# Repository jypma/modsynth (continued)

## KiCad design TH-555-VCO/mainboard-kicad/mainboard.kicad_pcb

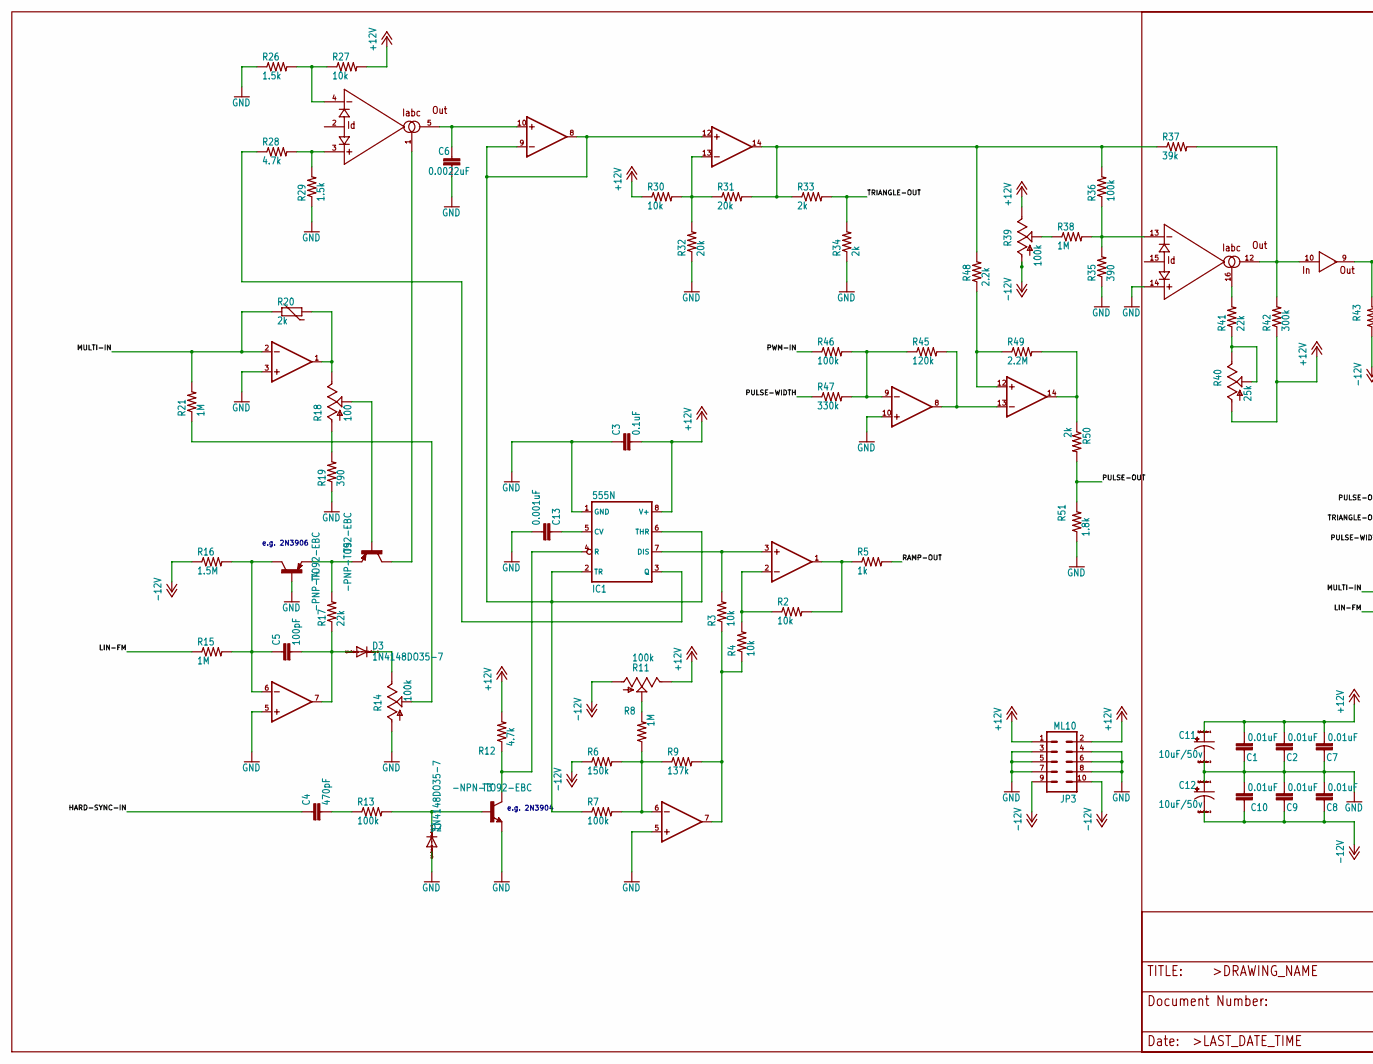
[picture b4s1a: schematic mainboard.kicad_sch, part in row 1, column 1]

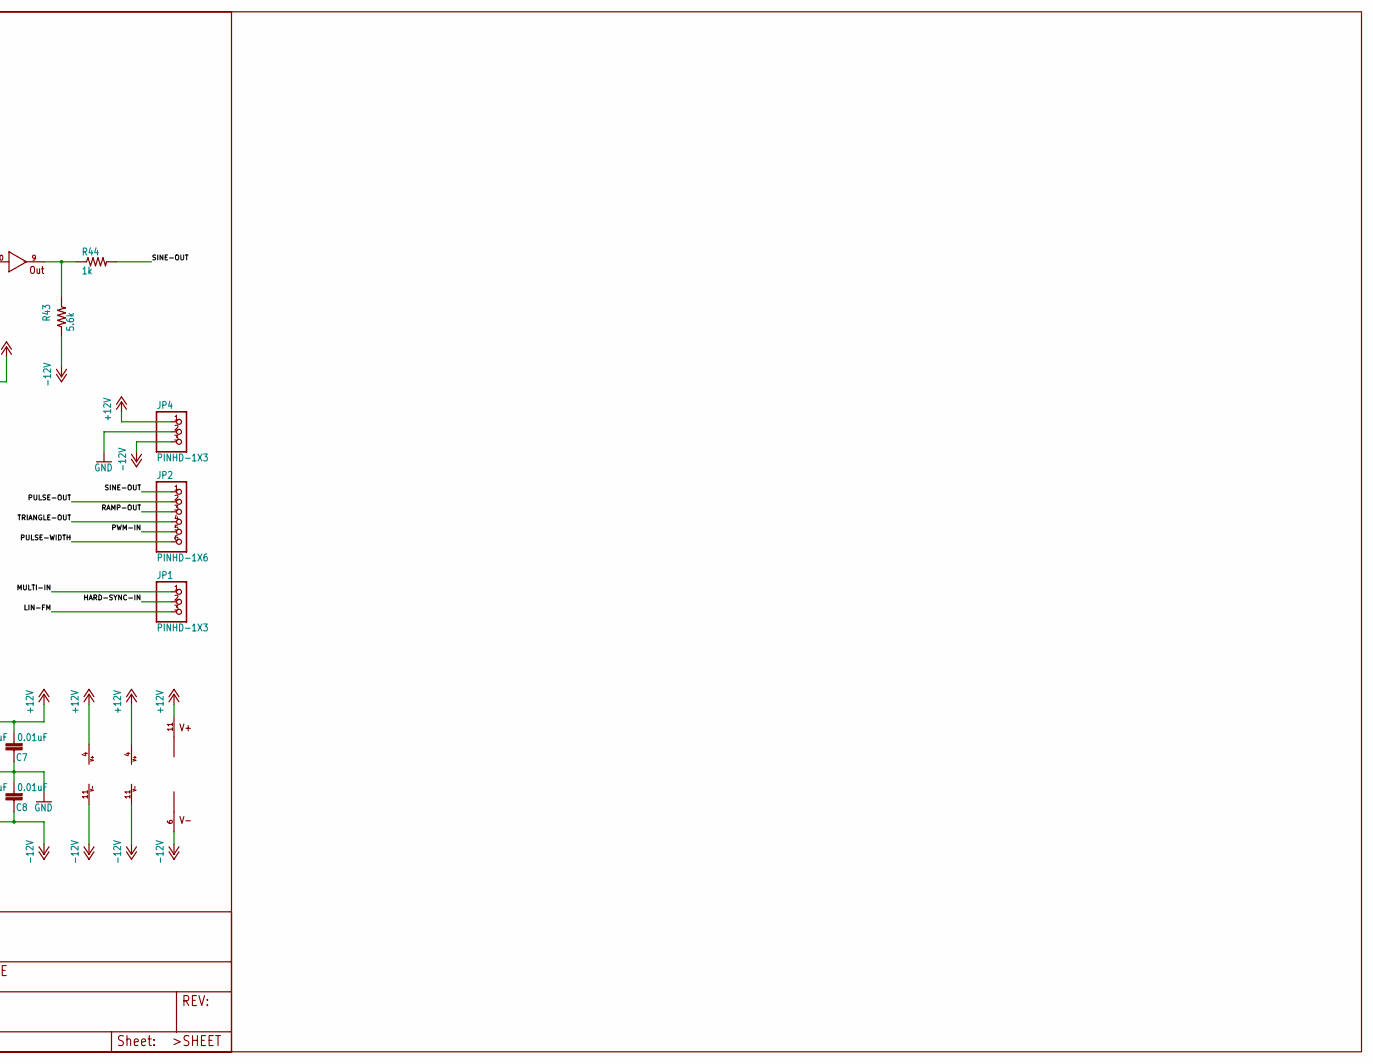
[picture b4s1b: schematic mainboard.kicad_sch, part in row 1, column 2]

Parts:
C1, C2, C7, C8, C9, C10: 0.01uF; C050-024X044
C3: 0.1uF; C050-024X044
C4: 470pF; C050-024X044
C5: 100pF; C050-024X044
C6: 0.0022uF; C050-025X075
C11, C12: 10uF/50v; E2,5-6
C13: 0.001uF; C050-024X044
D2, D3: 1N4148DO35-7; DO35-7
IC1: 555N; DIL08
IC2: LM13700N; SO-16_5.3x10.2mm_P1.27mm
IC3, IC4: TL074P; SO-14_5.3x10.2mm_P1.27mm
JP1, JP4: PINHD-1X3; 1X03
JP2: PINHD-1X6; 1X06
JP3: ML10
R2, R3, R4, R27, R30: 10k; 0204_7
R5, R44: 1k; 0204_7
R6: 150k; 0204_7
R7, R13, R36, R46: 100k; 0204_7
R8, R15, R21, R38: 1M; 0204_7
R9: 137k; 0204_7
R11, R14, R39: 100k; RJ9W
R12, R28: 4.7k; 0204_7
R16: 1.5M; 0204_7
R17, R41: 22k; 0204_7
R18: 100; RJ9W
R19, R35: 390; 0204_7
R20: 2k; R-5
R26, R29: 1.5k; 0204_7
R31, R32: 20k; 0204_7
R33, R34, R50: 2k; 0204_7
R37: 39k; 0204_7
R40: 25k; RJ9W
R42: 300k; 0204_7
R43: 5.6k; 0204_7
R45: 120k; 0204_7
R47: 330k; 0204_7
R48: 2.2k; 0204_7
R49: 2.2M; 0204_7
R51: 1.8k; 0204_7
T3: -NPN-TO92-EBC; TO92-EBC
T4, T5: -PNP-TO92-EBC; TO92-EBC

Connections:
+12V: C1.2, C2.2, C3.2, C7.2, C11.+, IC1.8 (V+), IC2.11 (V+), IC3.4 (V+), IC4.4 (V+), JP3.1, JP3.2, JP4.1, R11.E, R12.2, R27.2, R30.1, R39.E, R40.A, R42.1
-12V: C8.1, C9.1, C10.1, C12.-, IC2.6 (V-), IC3.11 (V-), IC4.11 (V-), JP3.9, JP3.10, JP4.3, R6.1, R11.A, R16.1, R39.A, R43.1
/HARD-SYNC-IN: C4.1, JP1.2
/LIN-FM: JP1.3, R15.1
/MULTI-IN: IC3.2 (-IN), JP1.1, R20.2, R21.2
/PULSE-OUT: JP2.2, R50.2, R51.2
/PULSE-WIDTH: JP2.6, R47.1
/PWM-IN: JP2.5, R46.1
/RAMP-OUT: JP2.3, R5.2
/SINE-OUT: JP2.1, R44.2
/TRIANGLE-OUT: JP2.4, R33.2, R34.2
GND: C1.1, C2.1, C3.1, C6.2, C7.1, C8.2, C9.2, C10.2, C11.-, C12.+, C13.1, D2.A, IC1.1 (GND), IC2.14 (+IN), IC3.3 (+IN), IC3.5 (+IN), IC4.5 (+IN), IC4.10 (+IN), JP3.3, JP3.4, JP3.5, JP3.6, JP3.7, JP3.8, JP4.2, R14.A, R19.1, R26.1, R29.1, R32.1, R34.1, R35.1, R51.1, T3.E, T4.B
unnamed: C4.2, R13.1
unnamed: C5.1, IC3.6 (-IN), R15.2, R16.2, T4.C
unnamed: C5.2, D3.A, IC3.7 (OUT), R17.1
unnamed: C6.1, IC2.5 (OUT), IC3.10 (+IN)
unnamed: C13.2, IC1.5 (CV)
unnamed: D2.C, R13.2, T3.B
unnamed: D3.C, R14.E
unnamed: IC1.2 (TR), IC1.6 (THR), IC3.8 (OUT), IC3.9 (-IN), IC4.12 (+IN), R7.1
unnamed: IC1.3 (Q), R28.1
unnamed: IC1.4 (R), R12.1, T3.C
unnamed: IC1.7 (DIS), IC4.3 (+IN), R3.2
unnamed: IC2.1 (IABC), T5.C
unnamed: IC2.3 (+IN), R28.2, R29.2
unnamed: IC2.4 (-IN), R26.2, R27.1
unnamed: IC2.9 (OUT), R43.2, R44.1
unnamed: IC2.10 (IN), IC2.12 (OUT), R37.2, R42.2
unnamed: IC2.13 (-IN), R35.2, R36.1, R38.2
unnamed: IC2.16 (IABC), R41.2
unnamed: IC3.1 (OUT), R18.E, R20.1
unnamed: IC3.12 (+IN), R48.1, R49.1
unnamed: IC3.13 (-IN), IC4.8 (OUT), R45.2
unnamed: IC3.14 (OUT), R49.2, R50.1
unnamed: IC4.1 (OUT), R2.2, R5.1
unnamed: IC4.2 (-IN), R2.1, R4.2
unnamed: IC4.6 (-IN), R6.2, R7.2, R8.1, R9.1
unnamed: IC4.7 (OUT), R3.1, R4.1, R9.2
unnamed: IC4.9 (-IN), R45.1, R46.2, R47.2
unnamed: IC4.13 (-IN), R30.2, R31.1, R32.2
unnamed: IC4.14 (OUT), R31.2, R33.1, R36.2, R37.1, R48.2
unnamed: R8.2, R11.S
unnamed: R14.S, R21.1
unnamed: R17.2, T4.E, T5.E
unnamed: R18.A, R19.2
unnamed: R18.S, T5.B
unnamed: R38.1, R39.S
unnamed: R40.E, R40.S, R41.1

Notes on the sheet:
e.g. 2N3904
e.g. 2N3906

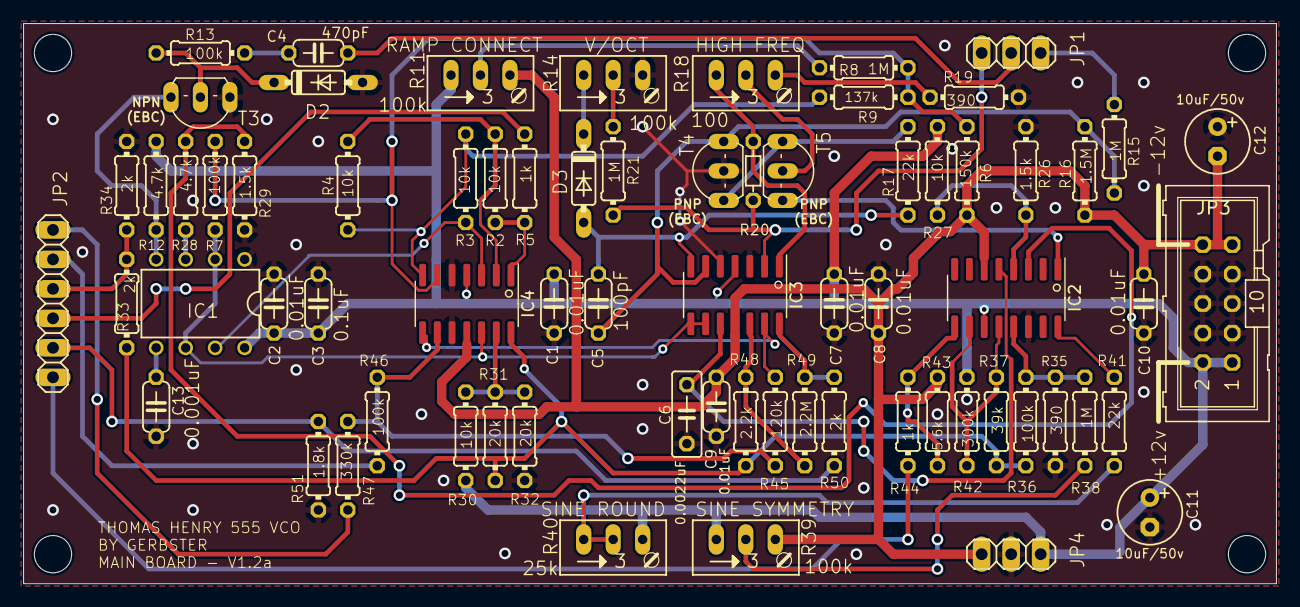
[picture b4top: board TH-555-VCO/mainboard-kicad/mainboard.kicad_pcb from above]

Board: 2 copper layers, 108.0 x 48.3 mm, 75 parts (0 on the bottom side), 48 nets.

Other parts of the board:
@HOLE0, @HOLE1, @HOLE2, @HOLE3: (no value)

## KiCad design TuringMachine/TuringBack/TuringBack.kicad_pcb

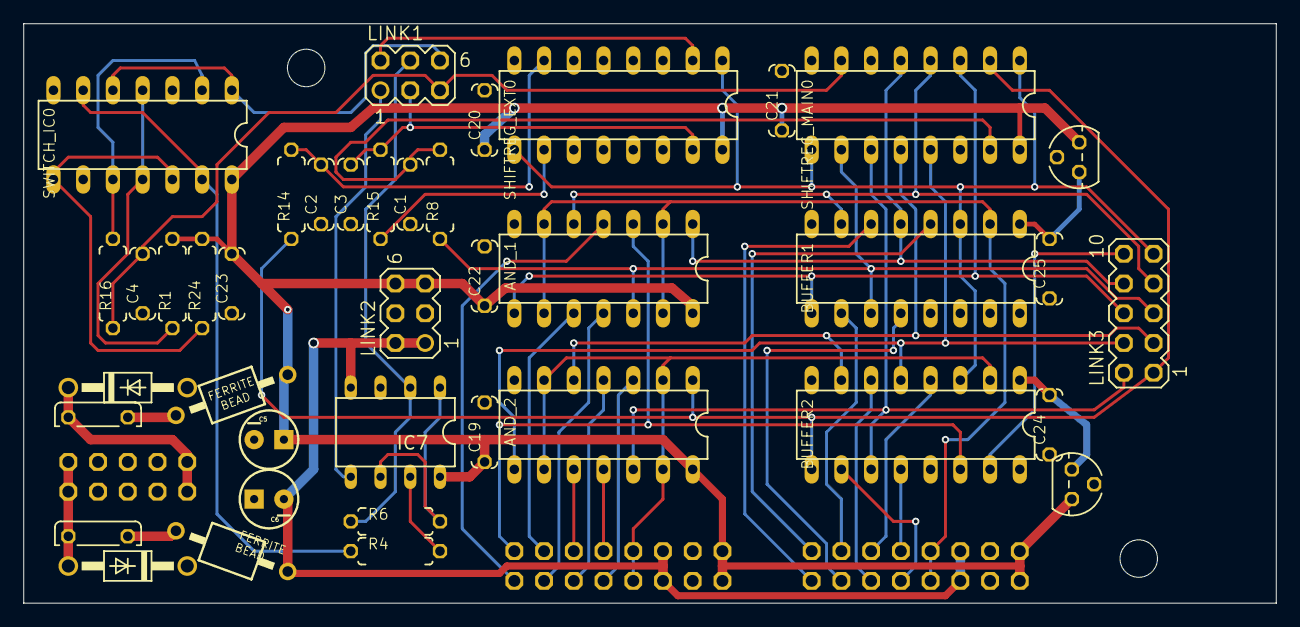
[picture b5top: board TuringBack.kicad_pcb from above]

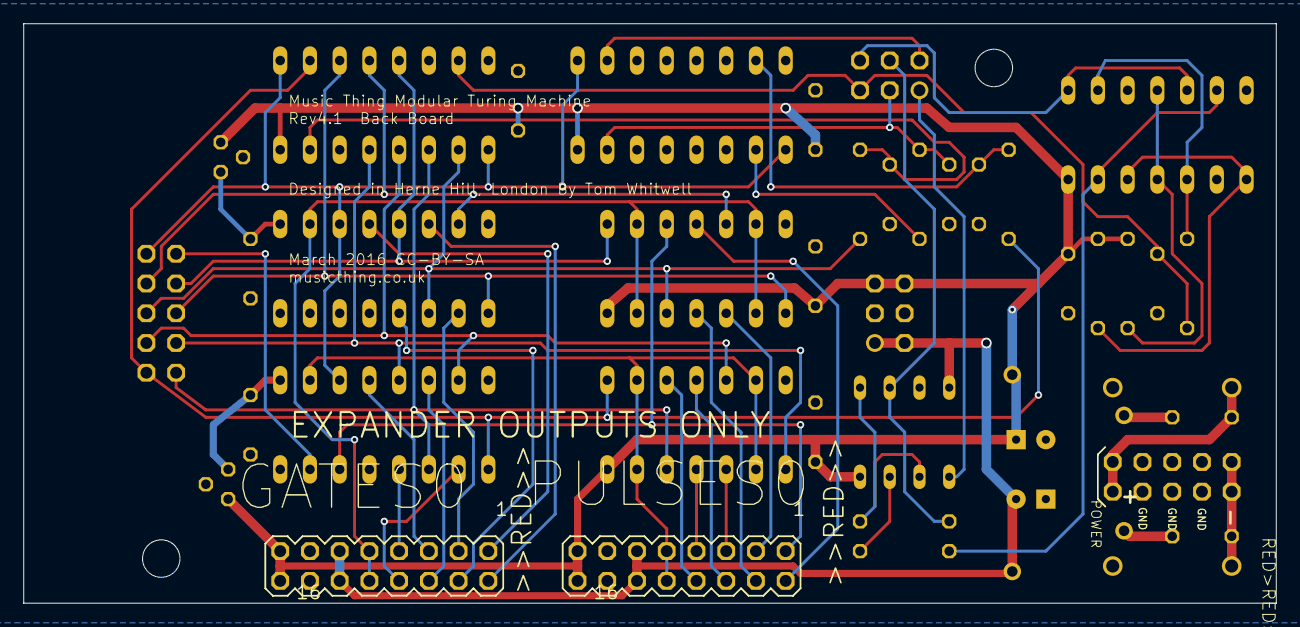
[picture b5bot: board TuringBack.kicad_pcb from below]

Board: 4 copper layers, 107.0 x 49.5 mm, 45 parts (3 on the bottom side), 52 nets.

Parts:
+FUSE0: +FUSE; C050H075X075
-FUSE0: -FUSE; C050H075X075
AND_1, AND_2: 4081; DIL14
BUFFER1, BUFFER2: 4050; DIL16
C1, C2, C3, C4: 1n; C050-024X044
C5, C6: 10uf; CPOL-RADIAL-10UF-25V
C19, C20, C21, C22, C23, C24, C25: 100n; C050-024X044
D5, D6: 1N4001; DO41-10
GATES0: MA08-2
IC7: TL072P; DIL08
IC11, IC12: 78L09; TO92
L1, L2: BL01RN1A
LINK1, LINK2: MA03-2
LINK3: MA05-2
PULSES0: MA08-2
R1, R8, R14, R15, R16, R24: 10k; 0207_7
R4: 100k; 0207_7
R6: 47k; 0207_7
SHIFTREG_EXT0: 4015; DIL16
SHIFTREG_MAIN0: 4015; DIL16
SV1: MA05-2
SWITCH_IC0: 4016; DIL14
U$4, U$5: MOUNTING_HOLE

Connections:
+9V_1: BUFFER2.1, C24.2, IC11.1
+9V_2: BUFFER1.1, C25.2, IC12.1
+12V_BACK: AND_1.14, AND_2.14, C5.1, C19.1, C20.1, C21.1, C22.1, C23.2, GATES0.15, GATES0.16, IC7.8, IC11.3, IC12.3, L1.2, LINK2.5, LINK2.6, PULSES0.15, PULSES0.16, R1.2, R24.2, SHIFTREG_EXT0.16, SHIFTREG_MAIN0.16, SWITCH_IC0.14
+12V_INLET: +FUSE0.1, D5.C, SV1.9, SV1.10
-12V_BACK: C6.2, GATES0.11, GATES0.12, IC7.4, L2.2, LINK2.1, LINK2.2, PULSES0.11, PULSES0.12
-12V_INLET: -FUSE0.1, D6.A, SV1.1, SV1.2
B1_BACK: AND_2.1, BUFFER2.9, LINK3.1, R14.1, SHIFTREG_MAIN0.2
B2_BACK: AND_2.12, BUFFER2.11, LINK3.2, SHIFTREG_MAIN0.11
B3_BACK: AND_2.5, BUFFER2.7, LINK3.3, SHIFTREG_MAIN0.12
B4_BACK: AND_2.8, BUFFER2.5, LINK3.4, SHIFTREG_MAIN0.13
B5_BACK: AND_1.12, BUFFER1.11, LINK3.5, R8.1, SHIFTREG_MAIN0.10
B6_BACK: AND_1.8, BUFFER1.9, LINK3.6, SHIFTREG_MAIN0.3
B7_BACK: AND_1.5, BUFFER1.7, LINK3.7, SHIFTREG_MAIN0.4
B8_BACK: AND_1.1, BUFFER1.5, LINK3.8, SHIFTREG_MAIN0.5
BUFFCLK2_BACK: AND_1.2, AND_1.6, AND_1.9, AND_1.13, BUFFER1.2, GATES0.9, GATES0.10
BUFFCLK_BACK: AND_2.2, AND_2.6, AND_2.9, AND_2.13, BUFFER2.2, PULSES0.9, PULSES0.10
CLOCK_BACK: BUFFER1.3, BUFFER2.3, LINK3.9, SHIFTREG_EXT0.1, SHIFTREG_EXT0.9, SHIFTREG_MAIN0.1, SHIFTREG_MAIN0.9
END_OF_LOOP_BACK: LINK1.6, SWITCH_IC0.1, SWITCH_IC0.5
GATE1: BUFFER1.4, GATES0.1
GATE2: BUFFER1.6, GATES0.2
GATE3: BUFFER1.10, GATES0.3
GATE4: BUFFER1.12, GATES0.4
GATE5: BUFFER2.4, GATES0.5
GATE6: BUFFER2.6, GATES0.6
GATE7: BUFFER2.12, GATES0.7
GATE8: BUFFER2.10, GATES0.8
GND_BACK: AND_1.7, AND_2.7, BUFFER1.8, BUFFER1.14, BUFFER2.8, C1.1, C2.1, C3.1, C4.1, C5.2, C6.1, C19.2, C20.2, C21.2, C22.2, C23.1, C24.1, C25.1, D5.A, D6.C, GATES0.13, GATES0.14, IC7.3, IC11.2, IC12.2, LINK2.3, LINK2.4, PULSES0.13, PULSES0.14, SHIFTREG_EXT0.6, SHIFTREG_EXT0.8, SHIFTREG_EXT0.14, SHIFTREG_MAIN0.6, SHIFTREG_MAIN0.8, SHIFTREG_MAIN0.14, SV1.3, SV1.4, SV1.5, SV1.6, SV1.7, SV1.8, SWITCH_IC0.3, SWITCH_IC0.7, SWITCH_IC0.9
LOOP_CTRL_BACK: IC7.2, LINK1.4, R6.1
unnamed: IC7.7, R4.2
unnamed: R4.1, SWITCH_IC0.6, SWITCH_IC0.13
unnamed: R1.1, SWITCH_IC0.4, SWITCH_IC0.11
unnamed: IC7.1, IC7.6, R6.2
unnamed: C1.2, R8.2, SHIFTREG_MAIN0.15
unnamed: R15.1, SHIFTREG_EXT0.10
unnamed: R16.2, SWITCH_IC0.2, SWITCH_IC0.10
unnamed: C2.2, R14.2, SHIFTREG_EXT0.7
unnamed: +FUSE0.2, L1.1
unnamed: -FUSE0.2, L2.1
unnamed: R24.1, SWITCH_IC0.8, SWITCH_IC0.12
NOISE_BACK: IC7.5, LINK1.1
PULSE1: AND_1.3, BUFFER2.14, PULSES0.1
PULSE2: AND_1.4, PULSES0.2
PULSE3: AND_1.10, PULSES0.3
PULSE4: AND_1.11, PULSES0.4
PULSE5: AND_2.10, PULSES0.5
PULSE6: AND_2.4, PULSES0.6
PULSE7: AND_2.11, PULSES0.7
PULSE8: AND_2.3, PULSES0.8
PULSE_OUT_BACK: BUFFER2.15, LINK3.10
START_OF_LOOP: C4.2, LINK1.5, R16.1, SHIFTREG_MAIN0.7
STEP_12_BACK: C3.2, LINK1.3, R15.2, SHIFTREG_EXT0.15
STEP_16_BACK: LINK1.2, SHIFTREG_EXT0.2
